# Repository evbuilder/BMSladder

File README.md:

# BMSladder
-----------
 BMS - cell at a time

This is an attempt at a single cell daisy chain Battery Management System. Emphasis is placed on minimum power draw and cost. Hopefully it is also reliable.

Most parts are over specified, however I worry that having the microcontroller powered directly from the cell could lead to bad things if the cell ever has a voltage spike on it. The type caused by a loose connection maybe especially bad.

Be warned.

Flashing the microcontroller
----------------------------
This uses a newer generation of ATtiny that is commonly used with Arduino. Current firmware uses Microchip Studio, and I have used a ATtiny416xplained demo board to flash the ATtiny202
Alternatively, firmware could be developed that uses Arduino IDE, with a programmer made as described here: https://github.com/SpenceKonde/AVR-Guidance/blob/master/UPDI/jtag2updi.md

History:
--------

v1.1
- incorporate uC pin swap mod
- improve connections

v1.0 Initial test production run. Mostly works. If you ever get one of these boards, check to see the modification is done to swap FAULT and EN pins.

Application: KiCad
Version: (5.1.10-1-10_14), release build

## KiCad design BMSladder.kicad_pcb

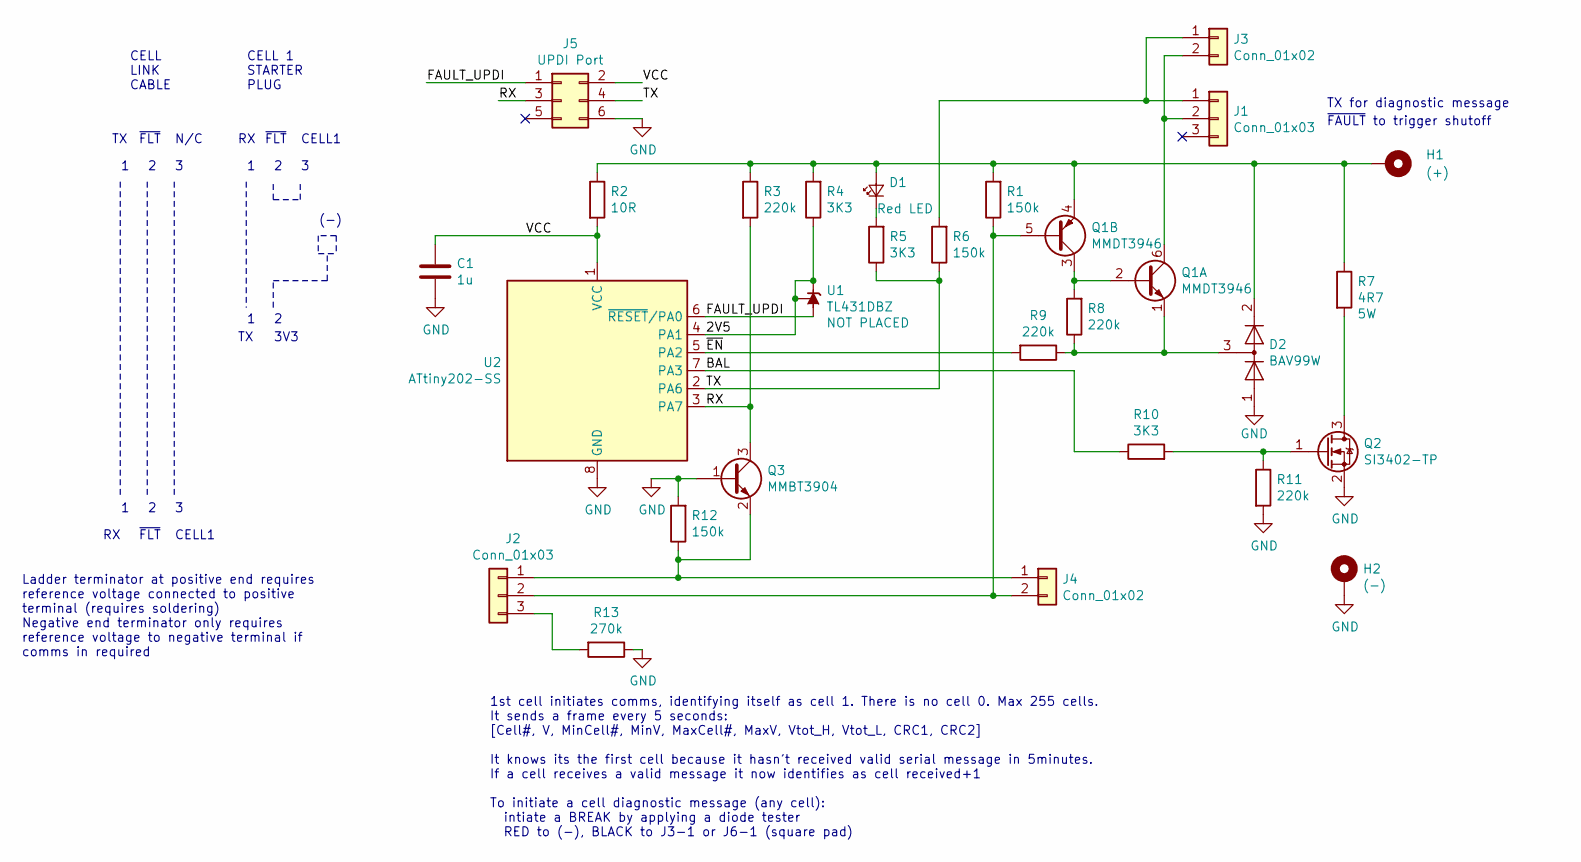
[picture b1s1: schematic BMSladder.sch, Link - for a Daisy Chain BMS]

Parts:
C1: 1u; C_0603_1608Metric
D1: Red LED; LED_0603_1608Metric
D2: BAV99W; SOT-323_SC-70
H1: (+); Terminal tag 3.2mm slot
H2: (-); Terminal tag 3.2mm slot
J1, J2: Conn_01x03; JST_SH_SM03B-SRSS-TB_1x03-1MP_P1.00mm_Horizontal
J3, J4: Conn_01x02; HY2.0mm2P_Header_Horizontal
J5: UPDI Port; PinHeader_2x03_P1.27mm_Vertical
Q1: MMDT3946; SOT-363_SC-70-6
Q2: SI3402-TP; SOT-23
Q3: MMBT3904; SOT-23
R1, R6, R12: 150k; R_0603_1608Metric
R2: 10R; R_0603_1608Metric
R3, R8, R9, R11: 220k; R_0603_1608Metric
R4, R5, R10: 3K3; R_0603_1608Metric
R7: 4R7; R_Axial_L17.0mm_D6.0mm_P22mm_Horizontal
R13: 270k; R_0603_1608Metric
U1: TL431DBZ; SOT-23
U2: ATtiny202-SS; SOIC-8_3.9x4.9mm_P1.27mm

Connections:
/2V5: R4.1, U1.1 (K), U1.2 (REF), U2.4 (PA1)
/BAL: R10.1, U2.7 (PA3)
/FAULT_UPDI: J5.1, U1.3 (A), U2.6 (~RESET~/PA0)
/RX: J5.3, Q3.3 (C), R3.2, U2.3 (PA7)
/TX: J5.4, R5.1, R6.1, U2.2 (PA6)
/VCC: C1.1, J5.2, R2.2, U2.1 (VCC)
/~EN: R9.2, U2.5 (PA2)
GND: C1.2, D2.1 (K), H2.1, J5.6, Q2.2 (S), Q3.1 (B), R11.2, R12.2, R13.1, U2.8 (GND)
unnamed: D1.1 (K), R5.2
unnamed: D1.2 (A), D2.2 (A), H1.1, Q1.4 (E2), R1.2, R2.1, R3.1, R4.2, R7.1
unnamed: D2.3 (K), Q1.1 (E1), R8.1, R9.1
unnamed: J1.1, J3.1, R6.2
unnamed: J1.2, J3.2, Q1.6 (C1)
unnamed: J2.1, J4.1, Q3.2 (E), R12.1
unnamed: J2.2, J4.2, Q1.5 (B2), R1.1
unnamed: J2.3, R13.2
unnamed: Q1.2 (B1), Q1.3 (C2), R8.2
unnamed: Q2.1 (G), R10.2, R11.1
unnamed: Q2.3 (D), R7.2

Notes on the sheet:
1st cell initiates comms, identifying itself as cell 1. There is no cell 0. Max 255 cells. It sends a frame every 5 seconds: [Cell#, V, MinCell#, MinV, MaxCell#, MaxV, Vtot_H, Vtot_L, CRC1, CRC2] It knows its the first cell because it hasn’t received valid serial message in 5minutes. If a cell rece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
TX for diagnostic message
~FAULT~ to trigger shutoff
N/C
~FLT
CELL1
CELL LINK CABLE
CELL 1 STARTER PLUG
Ladder terminator at positive end requires reference voltage connected to positive terminal (requires soldering) Negative end terminator only requires reference voltage to negative terminal if comms in required
(-)
3V3

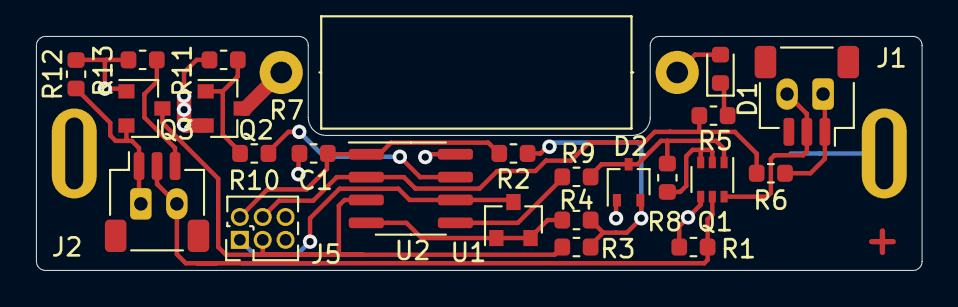
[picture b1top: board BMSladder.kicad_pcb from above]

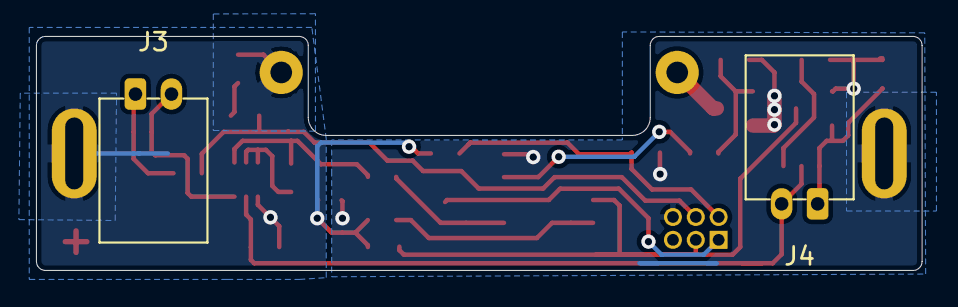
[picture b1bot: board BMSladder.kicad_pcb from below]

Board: 2 copper layers, 49.2 x 13.0 mm, 28 parts (2 on the bottom side), 19 nets.

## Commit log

2022-02-22 Version 1
2022-05-09 Update BMSladder.sch
    Added construction notes for further clarification
2022-07-21 Add firmware kindly supplied by Hein
2022-07-30 Balance at low current starts at 4.1V, switches to high current balance at 4.15V. Fault line is high for both overvoltage and undervoltage, but not for balance above 4.1V
2022-11-22 Improve connections
    Most fiddly thing with v1.0 was the tail and connectors. changing to a surface mount connector (easy assembly), commonly available lead (if modified to remove one wire).
    Also, uC pin swap as per Heins mod
2023-05-04 old changes kept just in case
    not sure why
2023-05-04 2023 version
    Links now sockets on both ends, cable has two plugs. Swapped pins to make voltage reference programming pin
2023-08-24 Tauis Settings
    LiFePO4 3.55V
    First time doesn't charge LED ON
    250mA current
2024-05-28 remove old top rung

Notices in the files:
BMSladder.kicad_pcb:
REV 1.1 (c) 2023 EHC
